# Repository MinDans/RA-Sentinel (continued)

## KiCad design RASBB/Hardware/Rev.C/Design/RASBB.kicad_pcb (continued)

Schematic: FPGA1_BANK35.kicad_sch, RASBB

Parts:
C182, C225, C261, C262, C263, C264, C265: 470nF; C_0402_1005Metric; Mfr. Part # GRT155R71A474KE01D; LCSC Part # C471404
C192: 47uF; C_0805_2012Metric; Mfr. Part # GRM21BR61A476ME15L; LCSC Part # C124129
C258: 100nF; C_0402_1005Metric; Mfr. Part # 0402B104K500CT; LCSC Part # C152814
C266, C267: 4.7uF; C_0402_1005Metric; Mfr. Part # GRM155R61A475KEAAD; LCSC Part # C77004
J16: Conn_01x02_Pin; PinHeader_1x02_P2.54mm_Vertical; Mfr. Part # PZ254V-11-02P; LCSC Part # C492401
R157, R158, R159: 49.9; R_0402_1005Metric; Mfr. Part # RMCF0402FT49R9; LCSC Part # C4229190
U10: XC7A100T-CSG324; BGA324C80P18X18_1500X1500X150; Mfr. Part # XC7A100T-2CSG324I; LCSC Part # C1521791
X3: OT2EL4C4JI-111OLP-50M; Oscillator_SMD_Abracon_ASE-4Pin_3.2x2.5mm; Mfr. Part # OT2EL4C4JI-111OLP-50M; LCSC Part # C5203552

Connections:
+1V8: C182.1, C192.2, C225.1, C261.1, C262.1, C263.1, C264.1, C265.1, C266.1, C267.1, R157.2, U10.A7 (VCCO_35), U10.C3 (VCCO_35), U10.D6 (VCCO_35), U10.F2 (VCCO_35), U10.G5 (VCCO_35), U10.J1 (VCCO_35); also elsewhere on the board
/PCIE/RX0_N: U10.J2 (IO_L22N_T3_35); also elsewhere on the board
/PCIE/RX0_P: U10.J3 (IO_L22P_T3_35); also elsewhere on the board
/PCIE/RX1_N: U10.K1 (IO_L23N_T3_35); also elsewhere on the board
/PCIE/RX1_P: U10.K2 (IO_L23P_T3_35); also elsewhere on the board
/PCIE/RX2_N: U10.G3 (IO_L20N_T3_35); also elsewhere on the board
/PCIE/RX2_P: U10.G4 (IO_L20P_T3_35); also elsewhere on the board
/PCIE/RX3_N: U10.G1 (IO_L17N_T2_35); also elsewhere on the board
/PCIE/RX3_P: U10.H1 (IO_L17P_T2_35); also elsewhere on the board
/PCIE/RX4_N: U10.G2 (IO_L15N_T2_DQS_35); also elsewhere on the board
/PCIE/RX4_P: U10.H2 (IO_L15P_T2_DQS_35); also elsewhere on the board
/PCIE/RX5_N: U10.E1 (IO_L18N_T2_35); also elsewhere on the board
/PCIE/RX5_P: U10.F1 (IO_L18P_T2_35); also elsewhere on the board
/PCIE/RX6_N: U10.F3 (IO_L13N_T2_MRCC_35); also elsewhere on the board
/PCIE/RX6_P: U10.F4 (IO_L13P_T2_MRCC_35); also elsewhere on the board
/PCIE/RX7_N: U10.A1 (IO_L9N_T1_DQS_AD7N_35); also elsewhere on the board
/PCIE/RX7_P: U10.B1 (IO_L9P_T1_DQS_AD7P_35); also elsewhere on the board
/PCIE/RX8_N: U10.E5 (IO_L5N_T0_AD13N_35); also elsewhere on the board
/PCIE/RX8_P: U10.E6 (IO_L5P_T0_AD13P_35); also elsewhere on the board
/PCIE/RX9_N: U10.B2 (IO_L10N_T1_AD15N_35); also elsewhere on the board
/PCIE/RX9_P: U10.B3 (IO_L10P_T1_AD15P_35); also elsewhere on the board
/PCIE/RX10_N: U10.C1 (IO_L16N_T2_35); also elsewhere on the board
/PCIE/RX10_P: U10.C2 (IO_L16P_T2_35); also elsewhere on the board
/PCIE/RX11_N: U10.A3 (IO_L8N_T1_AD14N_35); also elsewhere on the board
/PCIE/RX11_P: U10.A4 (IO_L8P_T1_AD14P_35); also elsewhere on the board
/PCIE/RX12_N: U10.D4 (IO_L11N_T1_SRCC_35); also elsewhere on the board
/PCIE/RX12_P: U10.D5 (IO_L11P_T1_SRCC_35); also elsewhere on the board
/PCIE/RX13_N: U10.A5 (IO_L3N_T0_DQS_AD5N_35); also elsewhere on the board
/PCIE/RX13_P: U10.A6 (IO_L3P_T0_DQS_AD5P_35); also elsewhere on the board
/PCIE/RX14_N: U10.B4 (IO_L7N_T1_AD6N_35); also elsewhere on the board
/PCIE/RX14_P: U10.C4 (IO_L7P_T1_AD6P_35); also elsewhere on the board
/PCIE/RX15_N: U10.B6 (IO_L2N_T0_AD12N_35); also elsewhere on the board
/PCIE/RX15_P: U10.B7 (IO_L2P_T0_AD12P_35); also elsewhere on the board
/PCIE/RX16_N: U10.C5 (IO_L1N_T0_AD4N_35); also elsewhere on the board
/PCIE/RX16_P: U10.C6 (IO_L1P_T0_AD4P_35); also elsewhere on the board
GND: C182.2, C192.1, C225.2, C258.2, C261.2, C262.2, C263.2, C264.2, C265.2, C266.2, C267.2, J16.2, X3.2 (GND); also elsewhere on the board
unnamed: J16.1, R159.1
unnamed: R159.2, U10.D3 (IO_L12N_T1_MRCC_35)
unnamed: R158.2, U10.E3 (IO_L12P_T1_MRCC_35)
unnamed: C258.1, R157.1, X3.1 (EN), X3.4 (Vdd)
unnamed: R158.1, X3.3 (OUT)

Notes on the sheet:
Clock Test Output

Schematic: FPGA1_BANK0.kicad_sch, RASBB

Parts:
C204: 100nF; C_0402_1005Metric; Mfr. Part # 0402B104K500CT; LCSC Part # C152814
C221: 47uF; C_0805_2012Metric; Mfr. Part # GRM21BR61A476ME15L; LCSC Part # C124129
C222: 470nF; C_0402_1005Metric; Mfr. Part # GRT155R71A474KE01D; LCSC Part # C471404
D11: DT2042-04SO-7; SOT95P285X140-6N; Mfr. Part # DT2042-04SO-7; LCSC Part # C2841428
D13, D15: A-SP192YR6C-C01-4T; LED_0603_1608Metric; Mfr. Part # A-SP192YR6C-C01-4T; LCSC Part # C5355433
J13: Conn_01x06_Socket; PinHeader_2x03_P1.27mm_Vertical_SMD; Mfr. Part # ZX-PZ1.27-2-3PWZ; LCSC Part # C41370771
R5, R54, R204: 4K7; R_0402_1005Metric; Mfr. Part # RC0402FR-074K7L; LCSC Part # C105871
R152, R153, R154, R155: 49.9; R_0402_1005Metric; Mfr. Part # RMCF0402FT49R9; LCSC Part # C4229190
R156: 10K; R_0402_1005Metric; Mfr. Part # WR04X1002FTL; LCSC Part # C163810
R205: 1.5K; R_0402_1005Metric; Mfr. Part # WR04X152JTL; LCSC Part # C384376
S2: B3FS-1002P; B3FS-1000P; Mfr. Part # B3FS-1002P; LCSC Part # C271750
U10: XC7A100T-CSG324; BGA324C80P18X18_1500X1500X150; Mfr. Part # XC7A100T-2CSG324I; LCSC Part # C1521791

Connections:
+3V3: C204.2, C221.1, C222.1, J13.6 (VCC), R5.1, R54.1, R156.1, R204.1, R205.1, U10.P8 (CFGBVS_0), U10.P12 (M0_0), U10.R9 (VCCO_0); also elsewhere on the board
/FPGA-01/BANK0/FPGA1_DONE: D13.1 (K), R205.2, U10.P10 (DONE_0); also elsewhere on the board
/FPGA-01/BANK0/FPGA1_INIT: D15.1 (K), R204.2, U10.P7 (INIT_B_0)
/FPGA-01/BANK0/FPGA1_TDO: R154.2, U10.E13 (TDO_0)
/FPGA-01/BANK0/JTAG1_TCK: R155.2, U10.E10 (TCK_0)
/FPGA-01/BANK0/JTAG1_TDI: R153.2, U10.E11 (TDI_0)
/FPGA-01/BANK0/JTAG1_TMS: R152.2, U10.E12 (TMS_0)
/FPGA-01/BANK0/TCK_1: D11.6 (I/O4), J13.4 (TCK_1), R155.1
/FPGA-01/BANK0/TDI_1: D11.4 (I/O3), J13.2 (TDI_2), R153.1
/FPGA-01/BANK0/TDO_1: D11.1 (I/O1), J13.3 (TDO_3), R154.1
/FPGA-01/BANK0/TMS_1: D11.3 (I/O2), J13.1 (TMS_1), R152.1
/FPGA-01/FPGA1_CLK: U10.E9 (CCLK_0); also elsewhere on the board
/FPGA-01/FPGA1_PROG: R156.2, S2.3 (B), S2.4 (B), U10.P9 (PROGRAM_B_0); also elsewhere on the board
GND: C204.1, C221.2, C222.2, D11.2 (VSS), J13.5 (GND), S2.1 (A), S2.2 (A), U10.J9 (VREFN_0), U10.J10 (VP_0), U10.K9 (VN_0), U10.K10 (VREFP_0), U10.L9 (DXN_0), U10.L10 (DXP_0), U10.P11 (M2_0), U10.P13 (M1_0); also elsewhere on the board
unnamed: D13.2 (A), R5.2
unnamed: D15.2 (A), R54.2

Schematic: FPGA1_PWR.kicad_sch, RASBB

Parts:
C184: 47uF; C_0805_2012Metric; Mfr. Part # GRM21BR61A476ME15L; LCSC Part # C124129
C185, C189, C190, C191, C193, C194, C196, C197, C200, C201, C203, C205, C207, C209: 470nF; C_0402_1005Metric; Mfr. Part # GRT155R71A474KE01D; LCSC Part # C471404
C198, C218, C220: 100uF; C_1206_3216Metric; Mfr. Part # GRM31CR61A107MEA8L; LCSC Part # C883598
C206, C208, C210, C211, C212, C213, C214, C215, C216, C217: 4.7uF; C_0402_1005Metric; Mfr. Part # GRM155R61A475KEAAD; LCSC Part # C77004
C219: 100uF; C_1206_3216Metric; Mfr. Part # GRM31CR61A107MEA8L; LCSC Part # C883598; not fitted
U10: XC7A100T-CSG324; BGA324C80P18X18_1500X1500X150; Mfr. Part # XC7A100T-2CSG324I; LCSC Part # C1521791

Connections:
+1V0: C185.1, C189.1, C190.1, C193.1, C194.1, C197.1, C198.1, C201.1, C205.1, C207.1, C209.1, C211.1, C212.1, C213.1, C214.1, C215.1, C216.1, C217.1, C218.1, C219.1, C220.1, U10.F8 (VCCINT), U10.F10 (VCCBRAM), U10.G7 (VCCINT), U10.G9 (VCCINT), U10.G11 (VCCBRAM), U10.H8 (VCCINT), U10.J7 (VCCINT), U10.J11 (VCCINT), U10.K8 (VCCINT), U10.L7 (VCCINT), U10.L11 (VCCINT), U10.M8 (VCCINT), U10.M10 (VCCINT), U10.N7 (VCCINT), U10.N9 (VCCINT), U10.N11 (VCCINT); also elsewhere on the board
+1V8: C184.1, C191.1, C196.1, C200.1, C203.1, C206.1, C208.1, C210.1, U10.E8 (VCCBATT_0), U10.F12 (VCCAUX), U10.H10 (VCCADC_0), U10.H12 (VCCAUX), U10.K12 (VCCAUX), U10.M12 (VCCAUX); also elsewhere on the board
GND: C184.2, C185.2, C189.2, C190.2, C191.2, C193.2, C194.2, C196.2, C197.2, C198.2, C200.2, C201.2, C203.2, C205.2, C206.2, C207.2, C208.2, C209.2, C210.2, C211.2, C212.2, C213.2, C214.2, C215.2, C216.2, C217.2, C218.2, C219.2, C220.2, U10.A2 (GND), U10.A12 (GND), U10.B5 (GND), U10.B15 (GND), U10.C8 (GND), U10.C18 (GND), U10.D1 (GND), U10.D11 (GND), U10.E4 (GND), U10.E14 (GND), U10.F7 (GND), U10.F9 (GND), U10.F11 (GND), U10.F17 (GND), U10.G8 (GND), U10.G10 (GND), U10.G12 (GND), U10.H3 (GND), U10.H7 (GND), U10.H9 (GNDADC_0), U10.H11 (GND), U10.H13 (GND), U10.J6 (GND), U10.J8 (GND), U10.J12 (GND), U10.J16 (GND), U10.K7 (GND), U10.K11 (GND), U10.L2 (GND), U10.L8 (GND), U10.L12 (GND), U10.M5 (GND), U10.M7 (GND), U10.M9 (GND), U10.M11 (GND), U10.M15 (GND), U10.N8 (GND), U10.N10 (GND), U10.N12 (GND), U10.N18 (GND), U10.P1 (GND), U10.R4 (GND), U10.R14 (GND), U10.T7 (GND), U10.T17 (GND), U10.U10 (GND), U10.V3 (GND), U10.V13 (GND); also elsewhere on the board

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
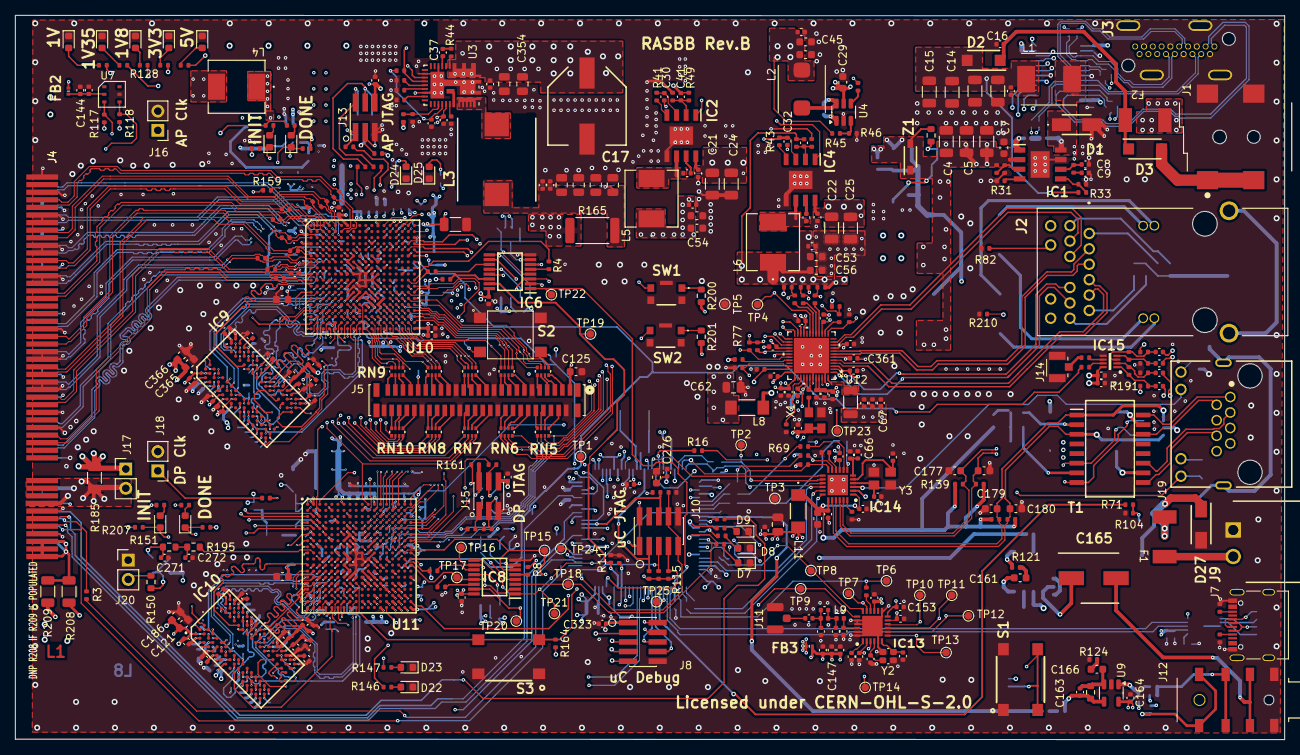
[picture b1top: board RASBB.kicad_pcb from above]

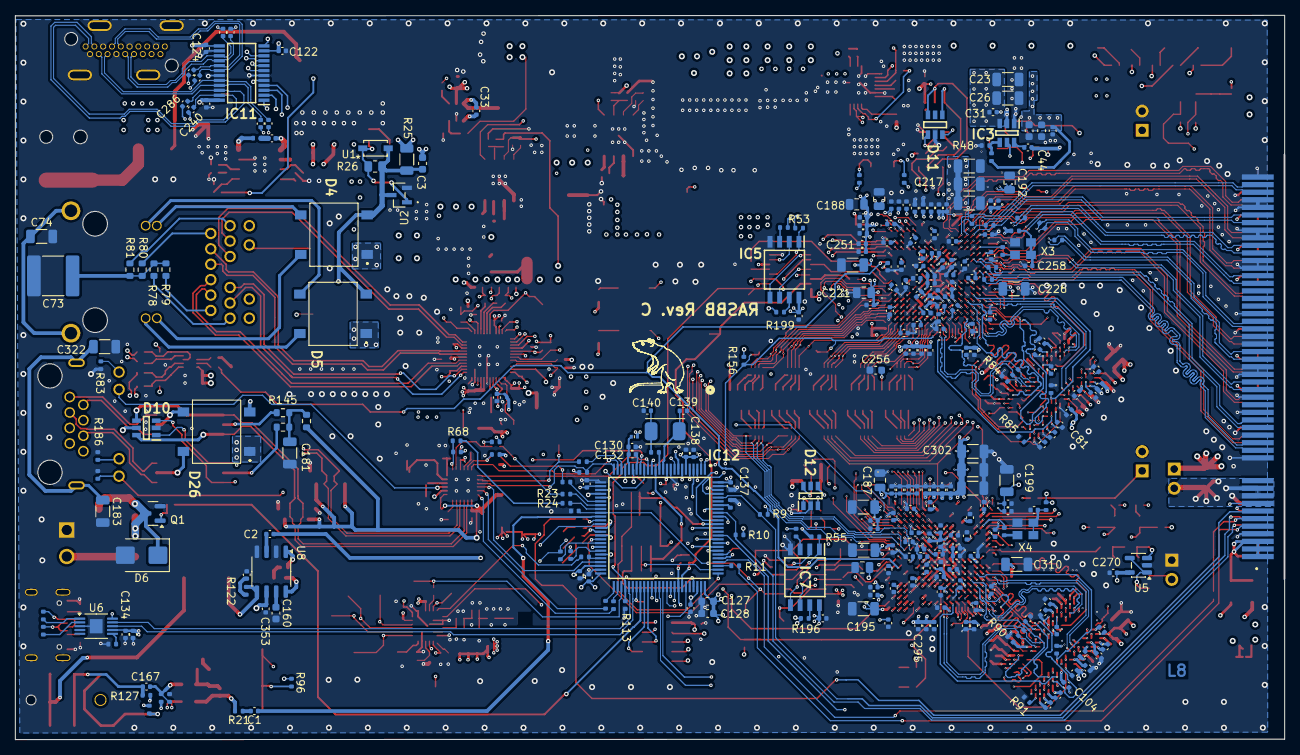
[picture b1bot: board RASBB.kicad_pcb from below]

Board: 8 copper layers, 167.2 x 95.4 mm, 707 parts (306 on the bottom side), 596 nets.

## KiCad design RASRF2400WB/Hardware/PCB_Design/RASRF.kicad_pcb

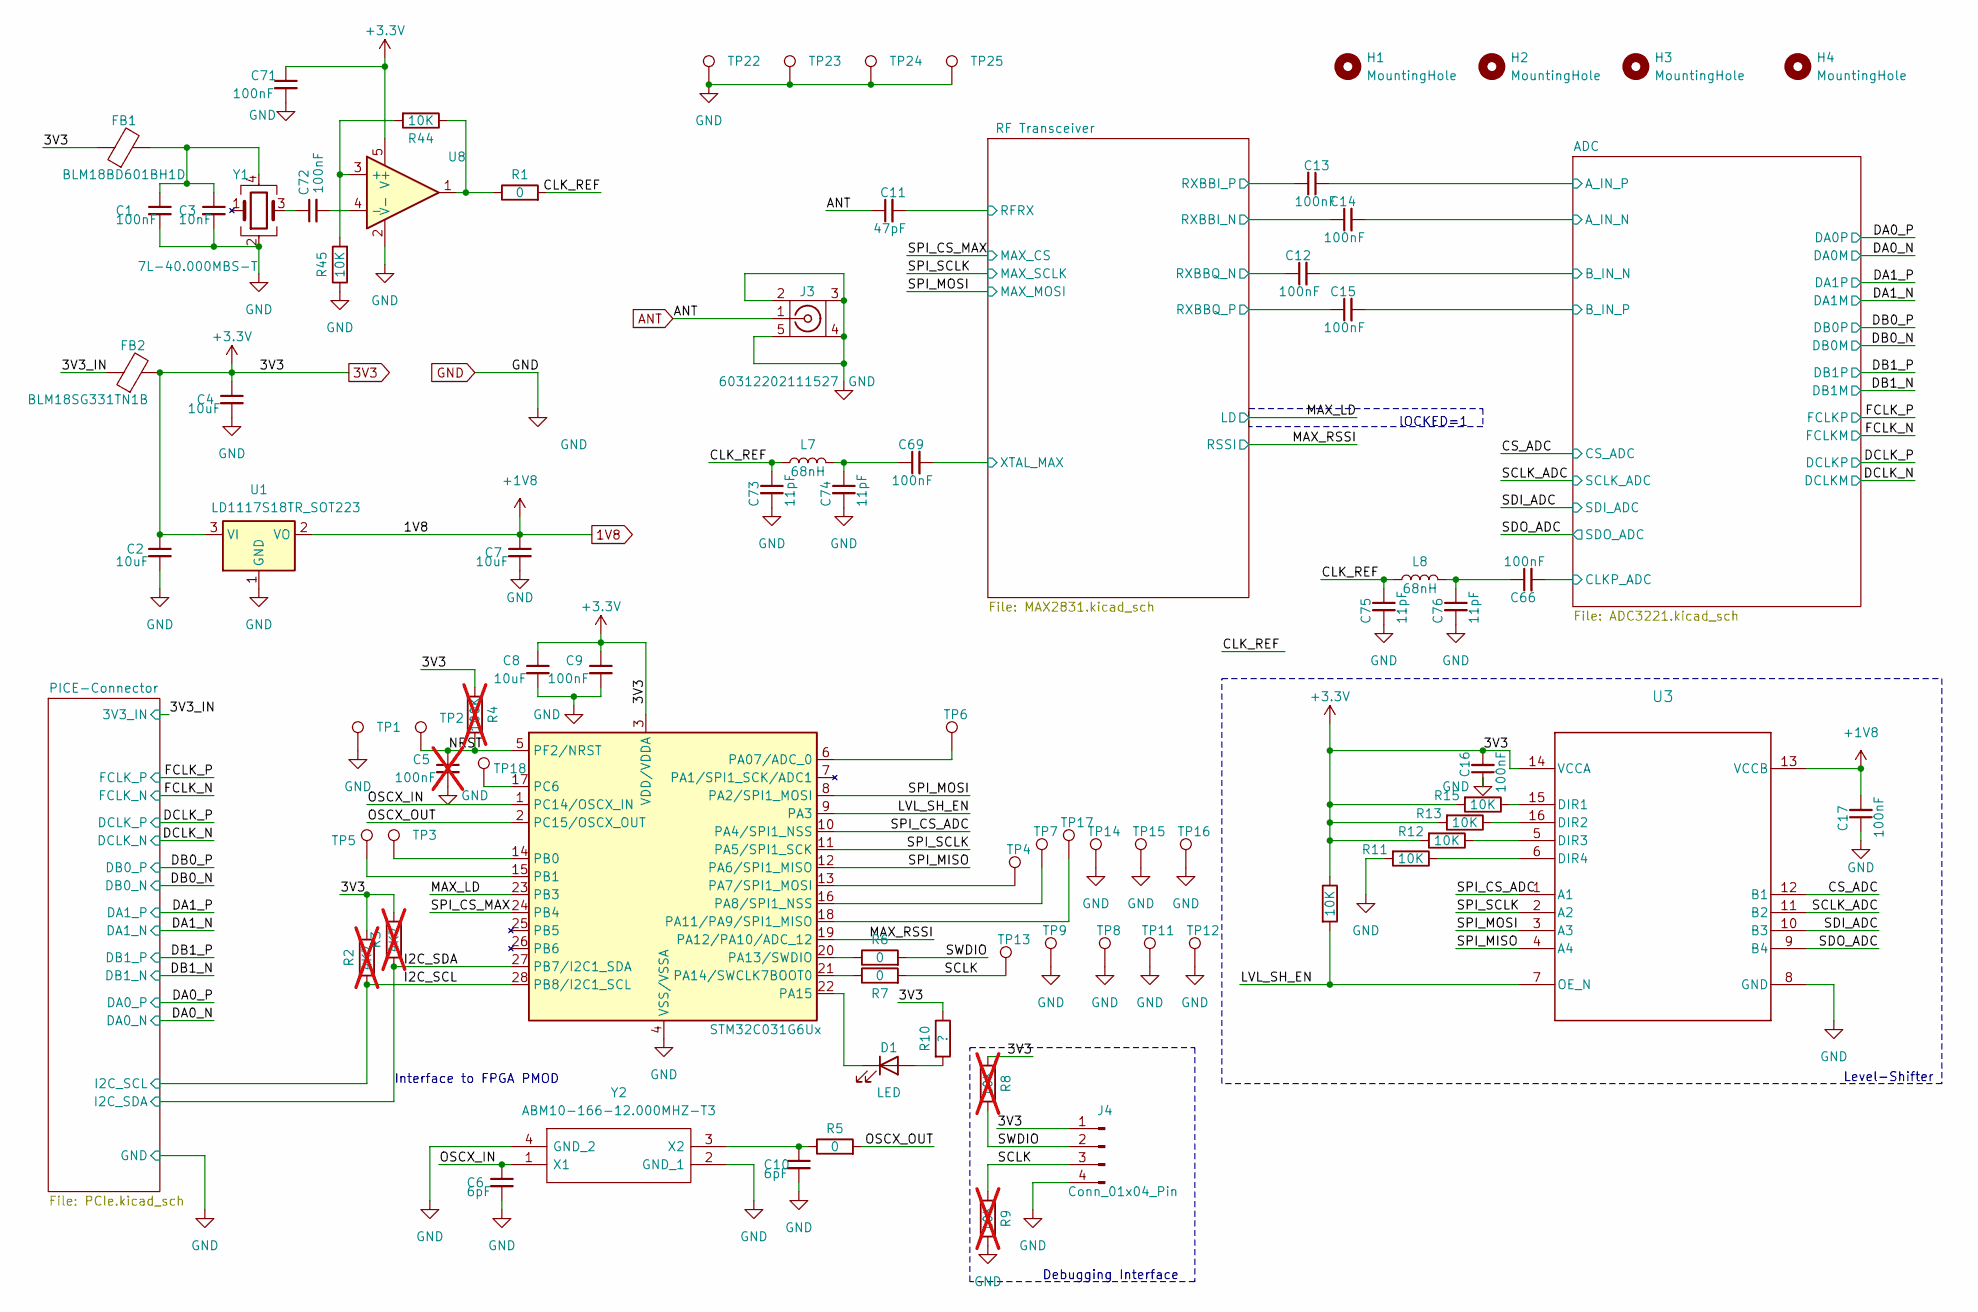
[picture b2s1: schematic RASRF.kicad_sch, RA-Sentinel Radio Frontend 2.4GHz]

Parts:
C1, C9, C12, C13, C14, C15, C16, C17, C66, C69, C71, C72: 100nF; C_0603_1608Metric
C2, C4, C7, C8: 10uF; C_0603_1608Metric
C3: 10nF; C_0603_1608Metric
C5: 100nF; C_0603_1608Metric; not fitted
C6, C10: 6pF; C_0603_1608Metric
C11: 47pF; C_0603_1608Metric
C73, C74, C75, C76: 11pF; C_0603_1608Metric
D1: LED; LED_0603_1608Metric
FB1: BLM18BD601BH1D; IND_BLM18_0603_MUR
FB2: BLM18SG331TN1B; IND_BLM18_0603_MUR
H1, H2, H3, H4: MountingHole; MountingHole_3.2mm_M3_ISO7380
J3: 60312202111527; JACK_02114307_WRE
J4: Conn_01x04_Pin; PinSocket_1x04_P2.54mm_Vertical
L7, L8: 68nH; L_0603_1608Metric
R1, R5, R6, R7: 0; R_0603_1608Metric
R2, R3: 4K7; R_0603_1608Metric; not fitted
R4: 100K; R_0603_1608Metric; not fitted
R8, R9: 10K; R_0603_1608Metric; not fitted
R10: ?; R_0603_1608Metric
R11, R12, R13, R14, R15, R44, R45: 10K; R_0603_1608Metric
TP1, TP8, TP11, TP12, TP14, TP15, TP16: TestPoint; TestPoint_THTPad_D1.0mm_Drill0.5mm
TP2, TP3, TP4, TP5, TP6, TP7, TP9, TP13, TP17, TP18: TestPoint; TestPoint_Pad_1.0x1.0mm
TP22, TP23, TP24, TP25: TestPoint; TestPoint_Pad_D1.5mm
U1: LD1117S18TR_SOT223; SOT-223-3_TabPin2
U2: STM32C031G6Ux; QFN-28_4x4mm_P0.5mm
U3: SN74AXC4T774RSVR; RSV0016A
U8: SOT-23-5
Y1: 7L-40.000MBS-T; 4-SMD_NoLead_Oscillator
Y2: ABM10-166-12.000MHZ-T3; ABM10; Mouser Part Number 815-ABM10-166-12T

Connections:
1V8: C7.1, C17.2, U1.2 (VO), U3.13 (VCCB); also elsewhere on the board
3V3: C2.1, C4.1, C8.1, C9.1, C16.2, C71.1, FB1.1, FB2.2, J4.1, R2.2, R3.1, R4.1, R8.1, R10.1, R12.2, R13.2, R14.1, R15.2, U1.3 (VI), U2.3 (VDD/VDDA), U3.14 (VCCA), U8.5 (V+); also elsewhere on the board
/3V3_IN: FB2.1; also elsewhere on the board
/ RF Transceiver/RFRX: C11.2; also elsewhere on the board
/ RF Transceiver/RXBBI_N: C14.1; also elsewhere on the board
/ RF Transceiver/RXBBI_P: C13.2; also elsewhere on the board
/ RF Transceiver/RXBBQ_N: C12.1; also elsewhere on the board
/ RF Transceiver/RXBBQ_P: C15.1; also elsewhere on the board
/ RF Transceiver/XTAL_MAX: C69.2; also elsewhere on the board
/ADC/A_IN_N: C14.2; also elsewhere on the board
/ADC/A_IN_P: C13.1; also elsewhere on the board
/ADC/B_IN_N: C12.2; also elsewhere on the board
/ADC/B_IN_P: C15.2; also elsewhere on the board
/ADC/CLKP_ADC: C66.2; also elsewhere on the board
/CLK_REF: C73.1, C75.1, L7.1, L8.1, R1.2
/CS_ADC: U3.12 (B1); also elsewhere on the board
/I2C_SCL: R2.1, U2.28 (PB8/I2C1_SCL); also elsewhere on the board
/I2C_SDA: R3.2, U2.27 (PB7/I2C1_SDA); also elsewhere on the board
/LVL_SH_EN: R14.2, U2.9 (PA3), U3.7 (OE_N)
/MAX_LD: U2.23 (PB3); also elsewhere on the board
/MAX_RSSI: U2.19 (PA12/PA10/ADC_12); also elsewhere on the board
/NRST: C5.1, R4.2, TP2.1, U2.5 (PF2/NRST)
/OSCX_IN: C6.1, U2.1 (PC14/OSCX_IN), Y2.1 (X1)
/OSCX_OUT: R5.2, U2.2 (PC15/OSCX_OUT)
/SCLK: J4.3, R7.2, R9.1, TP13.1
/SCLK_ADC: U3.11 (B2); also elsewhere on the board
/SDI_ADC: U3.10 (B3); also elsewhere on the board
/SDO_ADC: U3.9 (B4); also elsewhere on the board
/SPI_CS_ADC: U2.10 (PA4/SPI1_NSS), U3.1 (A1)
/SPI_CS_MAX: U2.24 (PB4); also elsewhere on the board
/SPI_MISO: U2.12 (PA6/SPI1_MISO), U3.4 (A4)
/SPI_MOSI: U2.8 (PA2/SPI1_MOSI), U3.3 (A3); also elsewhere on the board
/SPI_SCLK: U2.11 (PA5/SPI1_SCK), U3.2 (A2); also elsewhere on the board
/SWDIO: J4.2, R6.2, R8.2
ANT: C11.1, J3.1
GND: C1.2, C2.2, C3.2, C4.2, C5.2, C6.2, C7.2, C8.2, C9.2, C10.2, C16.1, C17.1, C71.2, C73.2, C74.2, C75.2, C76.2, J3.2, J3.3, J3.4, J3.5, J4.4, R9.2, R11.2, R45.1, TP1.1, TP8.1, TP9.1, TP11.1, TP12.1, TP14.1, TP15.1, TP16.1, TP22.1, TP23.1, TP24.1, TP25.1, U1.1 (GND), U2.4 (VSS/VSSA), U3.8 (GND), U8.2 (V-), Y1.2, Y2.2 (GND_1), Y2.4 (GND_2); also elsewhere on the board
unnamed: C1.1, C3.1, FB1.2, Y1.4
unnamed: C66.1, C76.1, L8.2
unnamed: C69.1, C74.1, L7.2
unnamed: C72.1, Y1.3
unnamed: D1.2 (A), R10.2
unnamed: D1.1 (K), U2.22 (PA15)
unnamed: R1.1, R44.1, U8.1
unnamed: TP6.1, U2.6 (PA07/ADC_0)
unnamed: TP4.1, U2.13 (PA7/SPI1_MOSI)
unnamed: TP7.1, U2.16 (PA8/SPI1_NSS)
unnamed: TP17.1, U2.18 (PA11/PA9/SPI1_MISO)
unnamed: R6.1, U2.20 (PA13/SWDIO)
unnamed: R7.1, U2.21 (PA14/SWCLK7BOOT0)
unnamed: TP3.1, U2.14 (PB0)
unnamed: TP5.1, U2.15 (PB1)
unnamed: TP18.1, U2.17 (PC6)
unnamed: R15.1, U3.15 (DIR1)
unnamed: R13.1, U3.16 (DIR2)
unnamed: R12.1, U3.5 (DIR3)
unnamed: R11.1, U3.6 (DIR4)
unnamed: R44.2, R45.2, U8.3 (+)
unnamed: C72.2, U8.4 (-)
unnamed: C10.1, R5.1, Y2.3 (X2)

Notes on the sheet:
Debugging Interface
Level-Shifter
Interface to FPGA PMOD
lOCKED=1

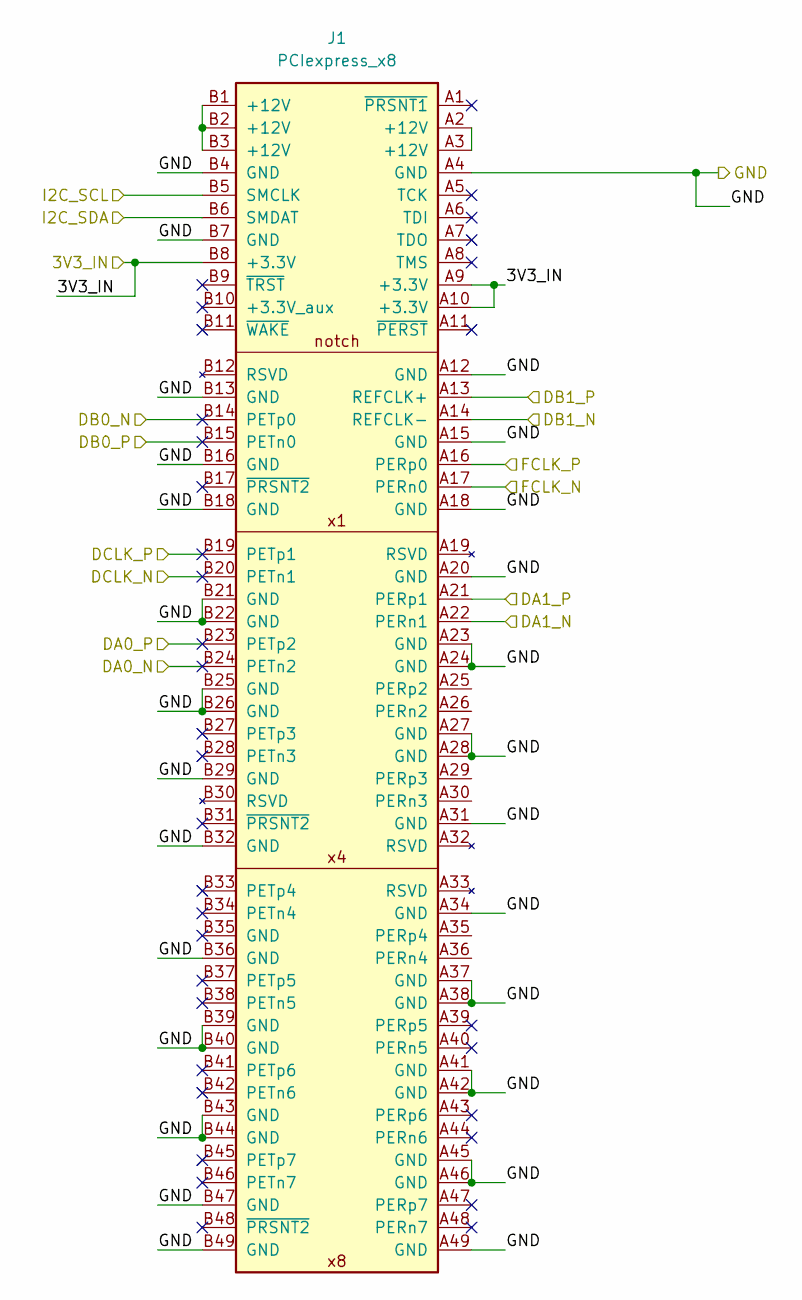
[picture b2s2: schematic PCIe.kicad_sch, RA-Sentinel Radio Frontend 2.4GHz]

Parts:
J1: PCIexpress_x8; BUS_PCIexpress_x8

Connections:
/3V3_IN: J1.A9 (+3.3V), J1.A10 (+3.3V), J1.B8 (+3.3V); also elsewhere on the board
/DA0_N: J1.B24 (PETn2); also elsewhere on the board
/DA0_P: J1.B23 (PETp2); also elsewhere on the board
/DA1_N: J1.A22 (PERn1); also elsewhere on the board
/DA1_P: J1.A21 (PERp1); also elsewhere on the board
/DB0_N: J1.B14 (PETp0); also elsewhere on the board
/DB0_P: J1.B15 (PETn0); also elsewhere on the board
/DB1_N: J1.A14 (REFCLK-); also elsewhere on the board
/DB1_P: J1.A13 (REFCLK+); also elsewhere on the board
/DCLK_N: J1.B20 (PETn1); also elsewhere on the board
/DCLK_P: J1.B19 (PETp1); also elsewhere on the board
/FCLK_N: J1.A17 (PERn0); also elsewhere on the board
/FCLK_P: J1.A16 (PERp0); also elsewhere on the board
/I2C_SCL: J1.B5 (SMCLK); also elsewhere on the board
/I2C_SDA: J1.B6 (SMDAT); also elsewhere on the board
GND: J1.A4 (GND), J1.A12 (GND), J1.A15 (GND), J1.A18 (GND), J1.A20 (GND), J1.A23 (GND), J1.A24 (GND), J1.A27 (GND), J1.A28 (GND), J1.A31 (GND), J1.A34 (GND), J1.A37 (GND), J1.A38 (GND), J1.A41 (GND), J1.A42 (GND), J1.A45 (GND), J1.A46 (GND), J1.A49 (GND), J1.B4 (GND), J1.B7 (GND), J1.B13 (GND), J1.B16 (GND), J1.B18 (GND), J1.B21 (GND), J1.B22 (GND), J1.B25 (GND), J1.B26 (GND), J1.B29 (GND), J1.B32 (GND), J1.B36 (GND), J1.B39 (GND), J1.B40 (GND), J1.B43 (GND), J1.B44 (GND), J1.B47 (GND), J1.B49 (GND); also elsewhere on the board
unnamed: J1.A2 (+12V), J1.A3 (+12V)
unnamed: J1.B1 (+12V), J1.B2 (+12V), J1.B3 (+12V)

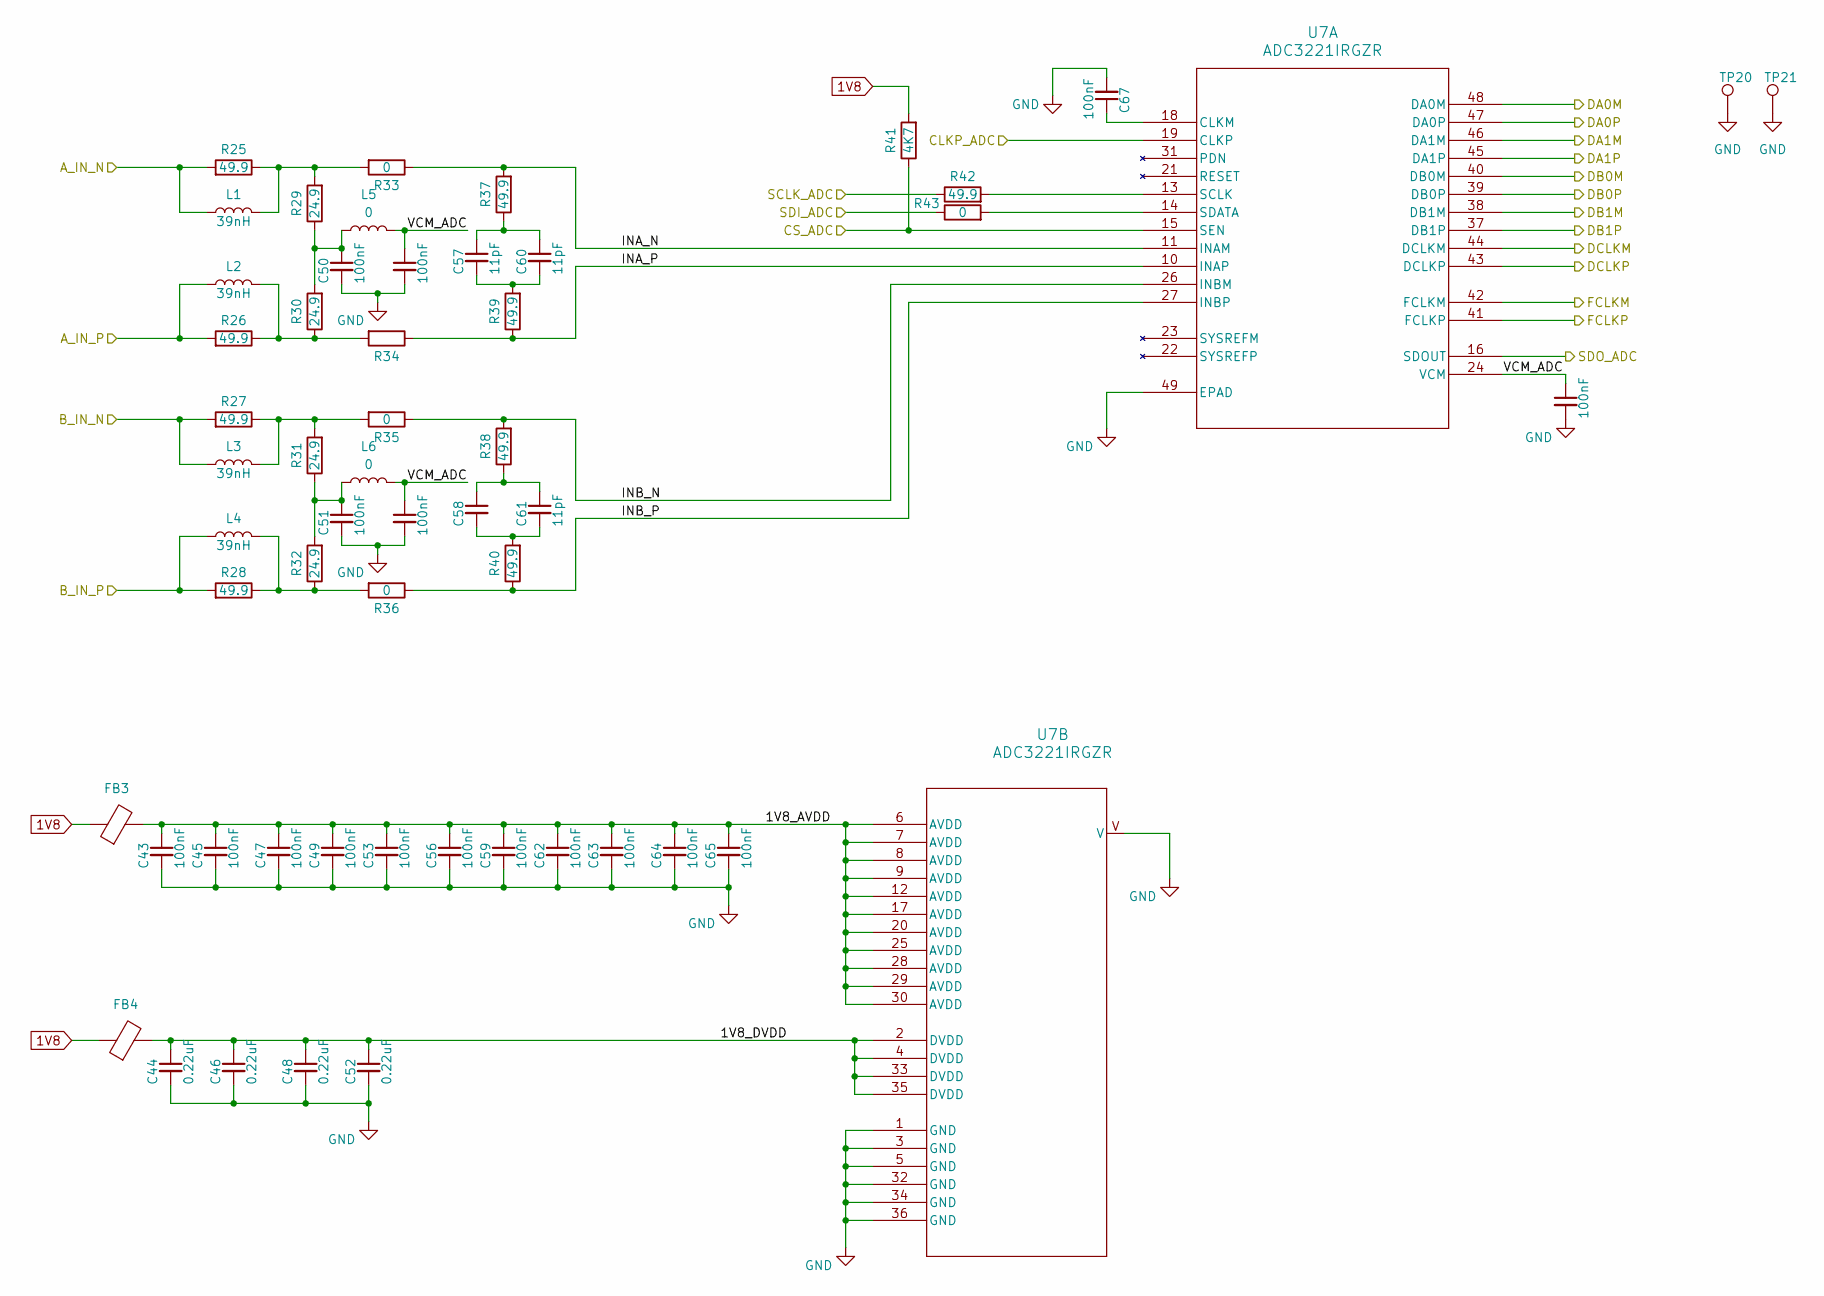
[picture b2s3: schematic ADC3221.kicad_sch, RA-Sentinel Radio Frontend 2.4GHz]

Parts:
C43, C45, C47, C49, C50, C51, C53, C54, C55, C56, C59, C62, C63, C64, C65, C67, C68: 100nF; C_0603_1608Metric
C44, C46, C48, C52: 0.22uF; C_0603_1608Metric
C57, C58, C60, C61: 11pF; C_0603_1608Metric
FB3, FB4: BLM41PG102SN1L; IND_BLM41_1806_MUR
L1, L2, L3, L4: 39nH; L_0603_1608Metric
L5, L6: 0; L_0603_1608Metric
R25, R26, R27, R28, R37, R38, R39, R40, R42: 49.9; R_0603_1608Metric
R29, R30, R31, R32: 24.9; R_0603_1608Metric
R33, R34, R35, R36, R43: 0; R_0603_1608Metric
R41: 4K7; R_0603_1608Metric
TP20, TP21: TestPoint; TestPoint_THTPad_D1.0mm_Drill0.5mm
U7: ADC3221IRGZR; RGZ48_TEX

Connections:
1V8: FB3.1, FB4.1, R41.2; also elsewhere on the board
/ADC/1V8_AVDD: C43.1, C45.1, C47.1, C49.1, C53.1, C56.1, C59.1, C62.1, C63.1, C64.1, C65.1, FB3.2, U7.6 (AVDD), U7.7 (AVDD), U7.8 (AVDD), U7.9 (AVDD), U7.12 (AVDD), U7.17 (AVDD), U7.20 (AVDD), U7.25 (AVDD), U7.28 (AVDD), U7.29 (AVDD), U7.30 (AVDD)
/ADC/1V8_DVDD: C44.1, C46.1, C48.1, C52.1, FB4.2, U7.2 (DVDD), U7.4 (DVDD), U7.33 (DVDD), U7.35 (DVDD)
/ADC/A_IN_N: L1.1, R25.2; also elsewhere on the board
/ADC/A_IN_P: L2.1, R26.2; also elsewhere on the board
/ADC/B_IN_N: L3.1, R27.2; also elsewhere on the board
/ADC/B_IN_P: L4.1, R28.2; also elsewhere on the board
/ADC/CLKP_ADC: U7.19 (CLKP); also elsewhere on the board
/ADC/INA_N: R33.1, R37.2, U7.11 (INAM)
/ADC/INA_P: R34.1, R39.1, U7.10 (INAP)
/ADC/INB_N: R35.1, R38.2, U7.26 (INBM)
/ADC/INB_P: R36.1, R40.1, U7.27 (INBP)
/ADC/VCM_ADC: C54.1, C55.1, C68.1, L5.2, L6.2, U7.24 (VCM)
/CS_ADC: R41.1, U7.15 (SEN); also elsewhere on the board
/DA0_N: U7.48 (DA0M); also elsewhere on the board
/DA0_P: U7.47 (DA0P); also elsewhere on the board
/DA1_N: U7.46 (DA1M); also elsewhere on the board
/DA1_P: U7.45 (DA1P); also elsewhere on the board
/DB0_N: U7.40 (DB0M); also elsewhere on the board
/DB0_P: U7.39 (DB0P); also elsewhere on the board
/DB1_N: U7.38 (DB1M); also elsewhere on the board
/DB1_P: U7.37 (DB1P); also elsewhere on the board
/DCLK_N: U7.44 (DCLKM); also elsewhere on the board
/DCLK_P: U7.43 (DCLKP); also elsewhere on the board
/FCLK_N: U7.42 (FCLKM); also elsewhere on the board
/FCLK_P: U7.41 (FCLKP); also elsewhere on the board
/SCLK_ADC: R42.1; also elsewhere on the board
/SDI_ADC: R43.1; also elsewhere on the board
/SDO_ADC: U7.16 (SDOUT); also elsewhere on the board
GND: C43.2, C44.2, C45.2, C46.2, C47.2, C48.2, C49.2, C50.2, C51.2, C52.2, C53.2, C54.2, C55.2, C56.2, C59.2, C62.2, C63.2, C64.2, C65.2, C67.2, C68.2, TP20.1, TP21.1, U7.1 (GND), U7.3 (GND), U7.5 (GND), U7.32 (GND), U7.34 (GND), U7.36 (GND), U7.49 (EPAD), U7.V; also elsewhere on the board
unnamed: C50.1, L5.1, R29.1, R30.2
unnamed: C51.1, L6.1, R31.1, R32.2
unnamed: C57.1, C60.1, R37.1
unnamed: C57.2, C60.2, R39.2
unnamed: C58.1, C61.1, R38.1
unnamed: C58.2, C61.2, R40.2
unnamed: L1.2, R25.1, R29.2, R33.2
unnamed: L2.2, R26.1, R30.1, R34.2
unnamed: L3.2, R27.1, R31.2, R35.2
unnamed: L4.2, R28.1, R32.1, R36.2
unnamed: C67.1, U7.18 (CLKM)
unnamed: R42.2, U7.13 (SCLK)
unnamed: R43.2, U7.14 (SDATA)

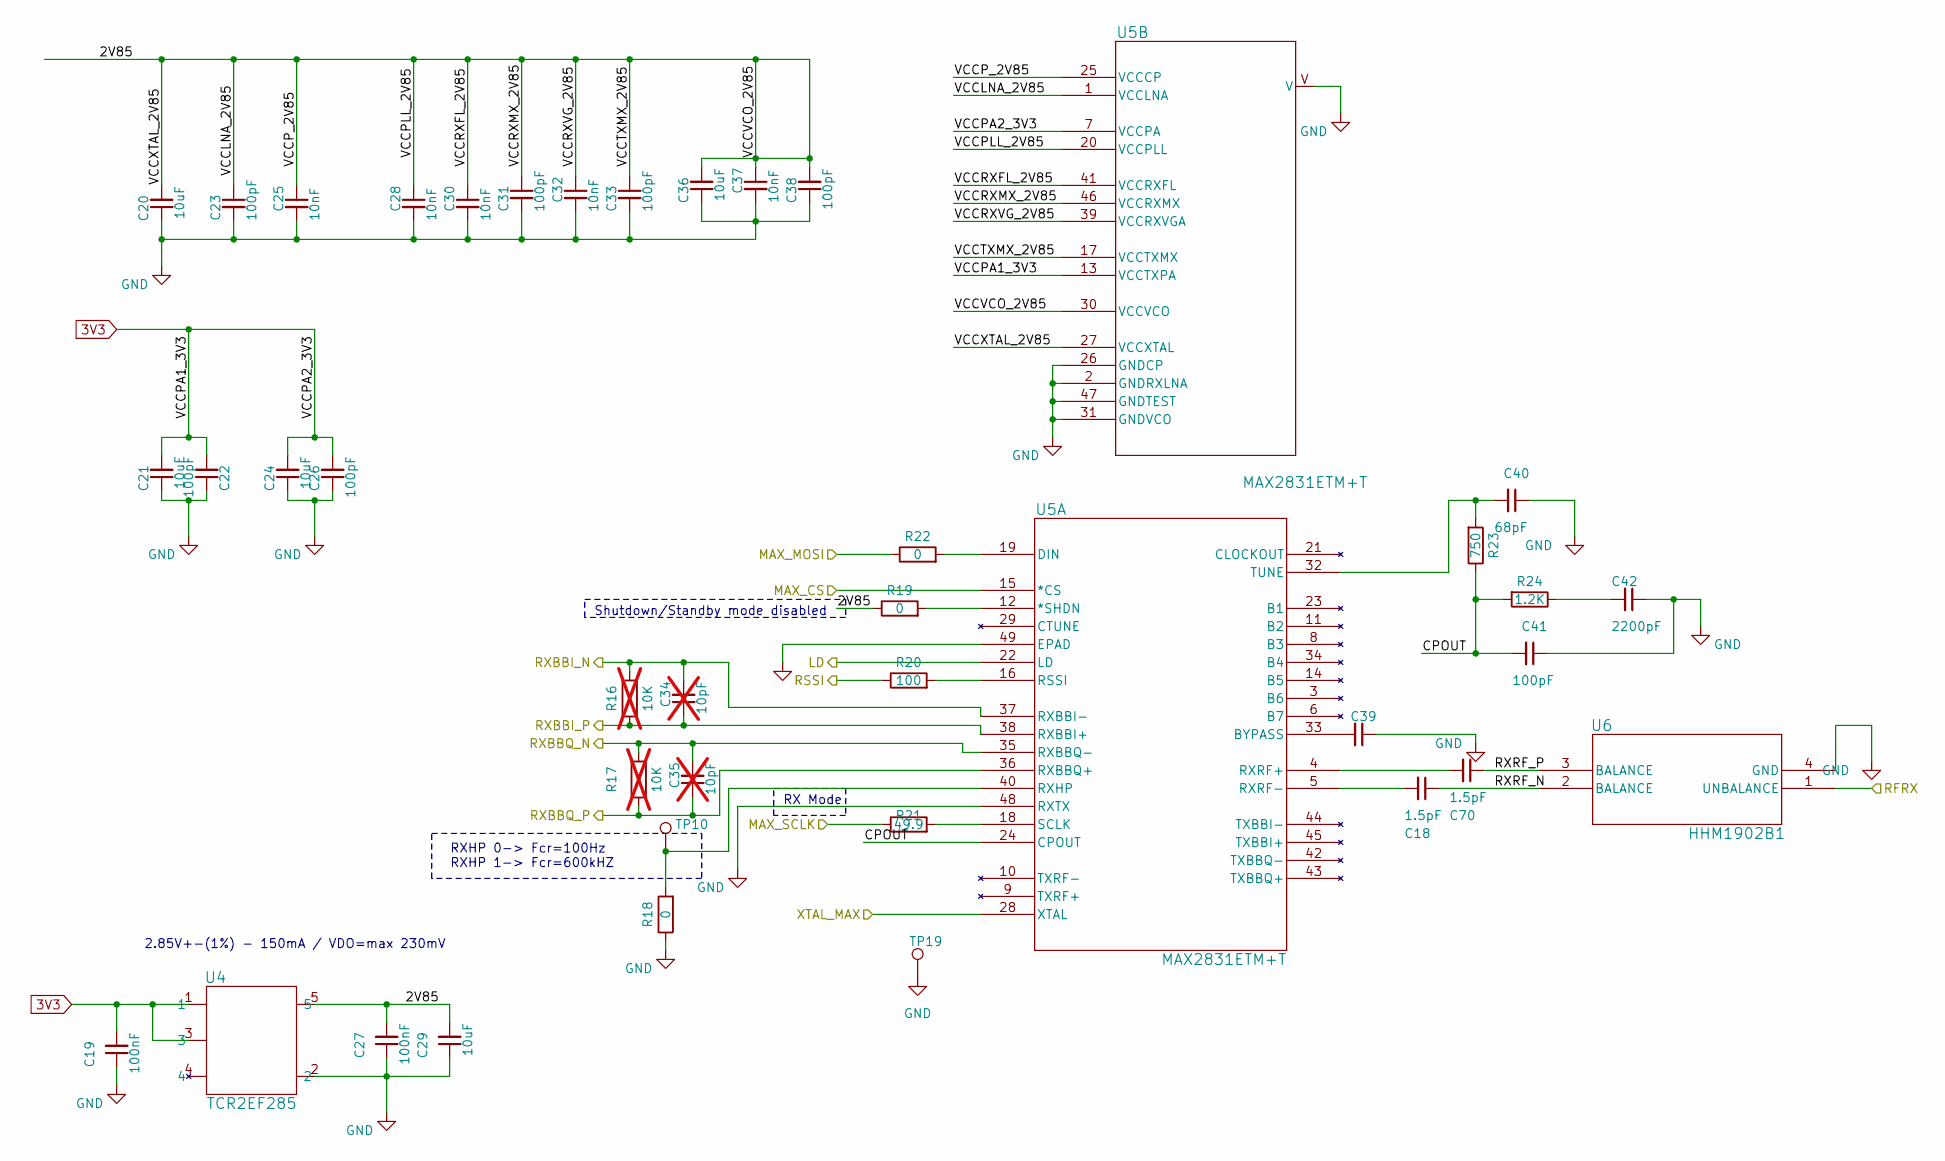
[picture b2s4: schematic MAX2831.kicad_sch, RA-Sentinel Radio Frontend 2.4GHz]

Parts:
C18, C70: 1.5pF; C_0603_1608Metric
C19, C27, C39: 100nF; C_0603_1608Metric
C20, C21, C24, C29, C36: 10uF; C_0603_1608Metric
C22, C23, C26, C31, C33, C38, C41: 100pF; C_0603_1608Metric
C25, C28, C30, C32, C37: 10nF; C_0603_1608Metric
C34, C35: 10pF; C_0603_1608Metric; not fitted
C40: 68pF; C_0603_1608Metric
C42: 2200pF; C_0603_1608Metric
R16, R17: 10K; R_0603_1608Metric; not fitted
R18, R19, R22: 0; R_0603_1608Metric
R20: 100; R_0603_1608Metric
R21: 49.9; R_0603_1608Metric
R23: 750; R_0603_1608Metric
R24: 1.2K; R_0603_1608Metric
TP10: TestPoint; TestPoint_Pad_1.0x1.0mm
TP19: TestPoint; TestPoint_Pad_D1.0mm
U4: TCR2EF285; SOT-25 SMV_TOS
U5: MAX2831ETM+T; 21-0144_T4877&plus_4_MXM
U6: HHM1902B1; HHM-4_1P0X0P5

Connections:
3V3: C19.2, C21.2, C22.2, C24.2, C26.2, U4.1, U4.3, U5.7 (VCCPA), U5.13 (VCCTXPA); also elsewhere on the board
/ RF Transceiver/2V85: C20.2, C23.1, C25.1, C27.2, C28.1, C29.2, C30.1, C31.1, C32.1, C33.1, C36.2, C37.1, C38.2, R19.1, U4.5, U5.1 (VCCLNA), U5.17 (VCCTXMX), U5.20 (VCCPLL), U5.25 (VCCCP), U5.27 (VCCXTAL), U5.30 (VCCVCO), U5.39 (VCCRXVGA), U5.41 (VCCRXFL), U5.46 (VCCRXMX)
/ RF Transceiver/CPOUT: C41.2, R23.1, R24.2, U5.24 (CPOUT)
/ RF Transceiver/RFRX: U6.1 (UNBALANCE); also elsewhere on the board
/ RF Transceiver/RXBBI_N: C34.2, R16.2, U5.37 (RXBBI-); also elsewhere on the board
/ RF Transceiver/RXBBI_P: C34.1, R16.1, U5.38 (RXBBI+); also elsewhere on the board
/ RF Transceiver/RXBBQ_N: C35.2, R17.2, U5.35 (RXBBQ-); also elsewhere on the board
/ RF Transceiver/RXBBQ_P: C35.1, R17.1, U5.36 (RXBBQ+); also elsewhere on the board
/ RF Transceiver/RXRF_N: C18.1, U6.2 (BALANCE)
/ RF Transceiver/RXRF_P: C70.1, U6.3 (BALANCE)
/ RF Transceiver/XTAL_MAX: U5.28 (XTAL); also elsewhere on the board
/MAX_LD: U5.22 (LD); also elsewhere on the board
/MAX_RSSI: R20.1; also elsewhere on the board
/SPI_CS_MAX: U5.15 (*CS); also elsewhere on the board
/SPI_MOSI: R22.1; also elsewhere on the board
/SPI_SCLK: R21.1; also elsewhere on the board
GND: C19.1, C20.1, C21.1, C22.1, C23.2, C24.1, C25.2, C26.1, C27.1, C28.2, C29.1, C30.2, C31.2, C32.2, C33.2, C36.1, C37.2, C38.1, C39.1, C40.1, C41.1, C42.1, R18.1, TP19.1, U4.2, U5.2 (GNDRXLNA), U5.26 (GNDCP), U5.31 (GNDVCO), U5.47 (GNDTEST), U5.48 (RXTX), U5.49 (EPAD), U5.V, U6.4 (GND); also elsewhere on the board
unnamed: C42.2, R24.1
unnamed: R19.2, U5.12 (*SHDN)
unnamed: C39.2, U5.33 (BYPASS)
unnamed: R22.2, U5.19 (DIN)
unnamed: R20.2, U5.16 (RSSI)
unnamed: R18.2, TP10.1, U5.40 (RXHP)
unnamed: C70.2, U5.4 (RXRF+)
unnamed: C18.2, U5.5 (RXRF-)
unnamed: R21.2, U5.18 (SCLK)
unnamed: C40.2, R23.2, U5.32 (TUNE)

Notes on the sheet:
2.85V+-(1%) - 150mA / VDO=max 230mV
Shutdown/Standby mode disabled
RX Mode
RXHP 0-> Fcr=100Hz RXHP 1-> Fcr=600kHZ
